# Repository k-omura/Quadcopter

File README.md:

# Quadcopter with PIC18F1230 and ESP8266.
Make a quadcopter from 0.  

PIC18F1230 as the BLDC driver and ESP 8266 as the central control unit.  
Do not use commercially available BLDC ESC.  

----------------------------

# BLDC driver
https://github.com/k-omura/SensorlessBLDC

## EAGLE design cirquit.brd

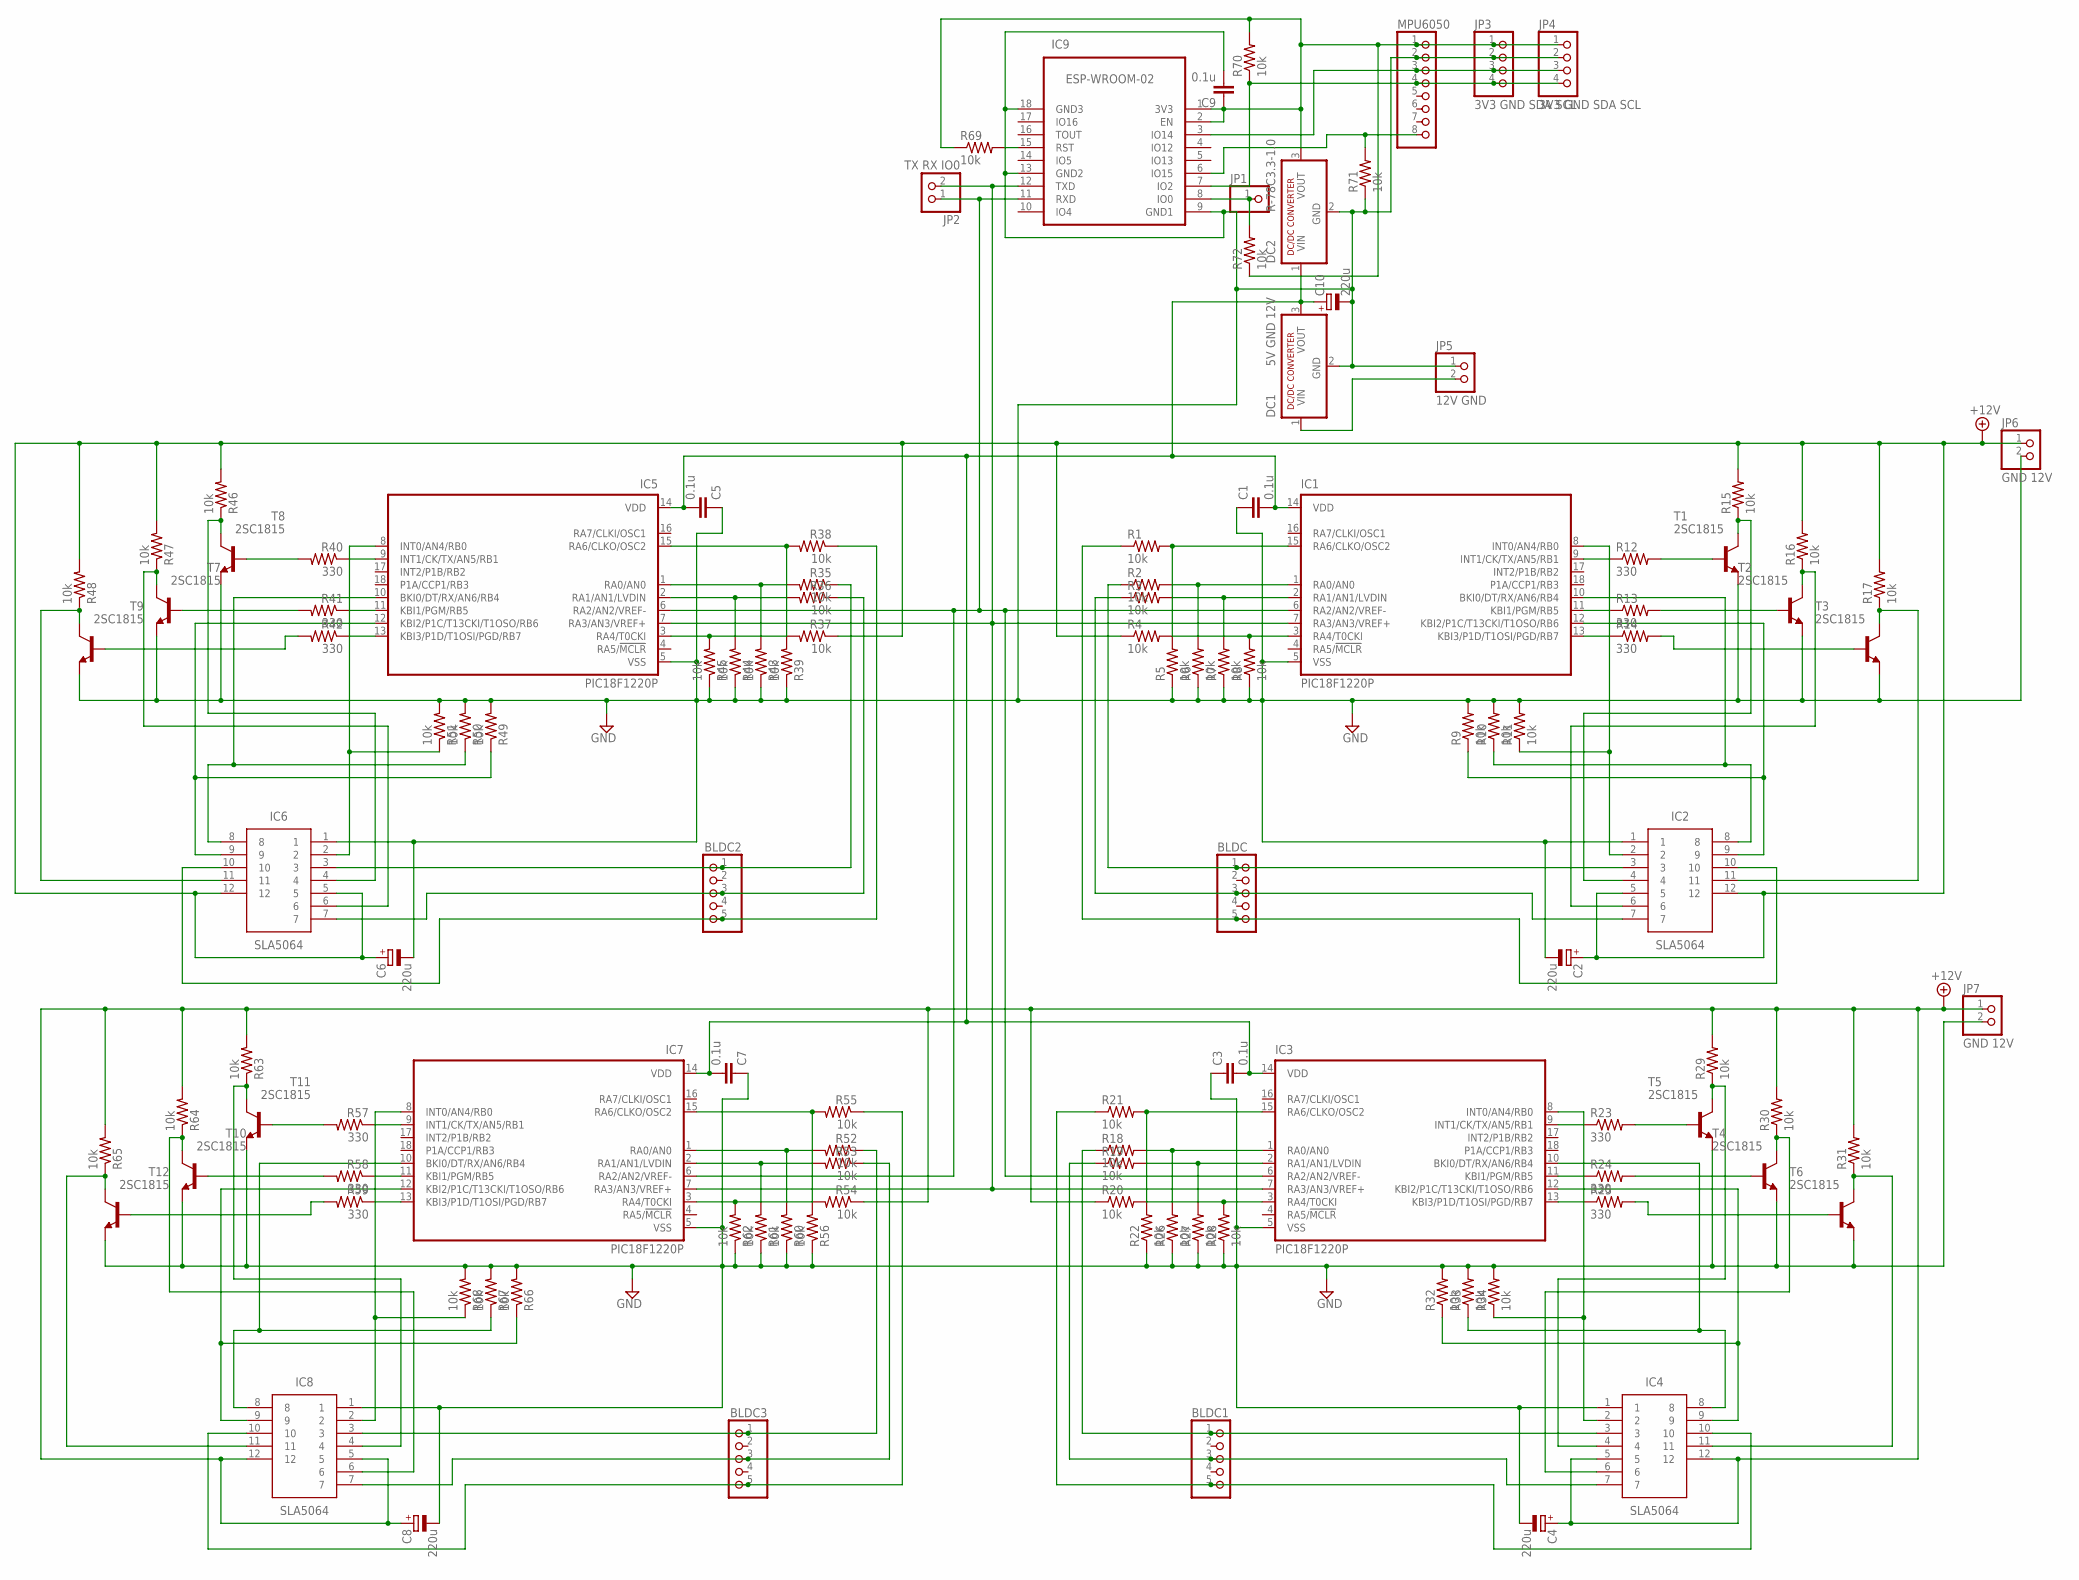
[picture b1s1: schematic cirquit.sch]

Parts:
BLDC, BLDC1, BLDC2, BLDC3: PINHD-1X5; 1X05
C1, C3, C5, C7, C9: 0.1u; C2.5-2
C2, C4, C6, C8, C10: 220u; E2,5-6E
DC1: 5V GND 12V; SIP3
DC2: R-78C3.3-1.0; SIP3
IC1, IC3, IC5, IC7: PIC18F1220P; DIL18
IC2, IC4, IC6, IC8: SLA5064; TO254P500X3150X1890-12P
IC9: ESP-WROOM-02; FRONT-FACE
JP1: PINHD-1X1; 1X01
JP2: TX RX IO0; 1X02
JP3, JP4: 3V3 GND SDA SCL; 1X04
JP5: 12V GND; 1X02
JP6, JP7: GND 12V; 1X02
MPU6050: PINHD-1X8; 1X08
R1, R2, R3, R4, R5, R6, R7, R8, R9, R10, R11, R15, R16, R17, R18, R19, R20, R21, R22, R26, R27, R28, R29, R30, R31, R32, R33, R34, R35, R36, R37, R38, R39, R43, R44, R45, R46, R47, R48, R49, R50, R51, R52, R53, R54, R55, R56, R60, R61, R62, R63, R64, R65, R66, R67, R68, R69, R70, R71, R72: 10k; 0204/7
R12, R13, R14, R23, R24, R25, R40, R41, R42, R57, R58, R59: 330; 0204/7
T1, T2, T3, T4, T5, T6, T7, T8, T9, T10, T11, T12: 2SC1815; TO92-ECB

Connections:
+12V: C2.+, C4.+, C6.+, C8.+, IC2.5, IC2.12, IC4.5, IC4.12, IC6.5, IC6.12, IC8.5, IC8.12, JP6.1, JP7.1, R4.1, R15.2, R16.2, R17.2, R20.1, R29.2, R30.2, R31.2, R37.1, R46.2, R47.2, R48.2, R54.1, R63.2, R64.2, R65.2
GND: C1.1, C2.-, C3.1, C4.-, C5.1, C6.-, C7.1, C8.-, C9.2, C10.-, DC1.2 (GND), DC2.2 (GND), IC1.5 (VSS), IC2.1, IC3.5 (VSS), IC4.1, IC5.5 (VSS), IC6.1, IC7.5 (VSS), IC8.1, IC9.9 (GND1), IC9.13 (GND2), IC9.18 (GND3), JP3.2, JP4.2, JP5.1, JP6.2, JP7.2, MPU6050.2, R5.1, R6.1, R7.1, R8.1, R9.2, R10.2, R11.2, R22.1, R26.1, R27.1, R28.1, R32.2, R33.2, R34.2, R39.1, R43.1, R44.1, R45.1, R49.2, R50.2, R51.2, R56.1, R60.1, R61.1, R62.1, R66.2, R67.2, R68.2, R71.1, T1.E, T2.E, T3.E, T4.E, T5.E, T6.E, T7.E, T8.E, T9.E, T10.E, T11.E, T12.E
unnamed: IC1.15 (RA6/CLKO/OSC2), R1.2, R5.2
unnamed: IC1.1 (RA0/AN0), R2.2, R6.2
unnamed: IC1.2 (RA1/AN1/LVDIN), R3.2, R7.2
unnamed: IC1.3 (RA4/T0CKI), R4.2, R8.2
unnamed: IC3.15 (RA6/CLKO/OSC2), R21.2, R22.2
unnamed: BLDC.1, IC2.3, R2.1
unnamed: BLDC.3, IC2.7, R3.1
unnamed: IC3.1 (RA0/AN0), R18.2, R26.2
unnamed: IC1.9 (INT1/CK/TX/AN5/RB1), R12.1
unnamed: IC1.11 (KBI1/PGM/RB5), R13.1
unnamed: IC1.13 (KBI3/P1D/T1OSI/PGD/RB7), R14.1
unnamed: R12.2, T1.B
unnamed: R13.2, T2.B
unnamed: R14.2, T3.B
unnamed: IC2.4, R15.1, T1.C
unnamed: IC2.6, R16.1, T2.C
unnamed: IC2.11, R17.1, T3.C
unnamed: IC3.2 (RA1/AN1/LVDIN), R19.2, R27.2
unnamed: IC3.3 (RA4/T0CKI), R20.2, R28.2
unnamed: BLDC1.1, IC4.3, R18.1
unnamed: BLDC1.3, IC4.7, R19.1
unnamed: IC1.8 (INT0/AN4/RB0), IC2.2, R11.1
unnamed: IC1.10 (BKI0/DT/RX/AN6/RB4), IC2.8, R10.1
unnamed: IC1.12 (KBI2/P1C/T13CKI/T1OSO/RB6), IC2.9, R9.1
unnamed: IC1.6 (RA2/AN2/VREF-), IC3.6 (RA2/AN2/VREF-), IC5.6 (RA2/AN2/VREF-), IC7.6 (RA2/AN2/VREF-), IC9.11 (RXD), JP2.1
unnamed: C1.2, C3.2, C5.2, C7.2, C10.+, DC1.3 (VOUT), DC2.1 (VIN), IC1.14 (VDD), IC3.14 (VDD), IC5.14 (VDD), IC7.14 (VDD)
unnamed: IC3.9 (INT1/CK/TX/AN5/RB1), R23.1
unnamed: IC3.11 (KBI1/PGM/RB5), R24.1
unnamed: BLDC.5, IC2.10, R1.1
unnamed: IC3.13 (KBI3/P1D/T1OSI/PGD/RB7), R25.1
unnamed: R23.2, T5.B
unnamed: R24.2, T4.B
unnamed: R25.2, T6.B
unnamed: IC4.4, R29.1, T5.C
unnamed: IC4.6, R30.1, T4.C
unnamed: IC4.11, R31.1, T6.C
unnamed: IC3.8 (INT0/AN4/RB0), IC4.2, R34.1
unnamed: IC3.10 (BKI0/DT/RX/AN6/RB4), IC4.8, R33.1
unnamed: IC3.12 (KBI2/P1C/T13CKI/T1OSO/RB6), IC4.9, R32.1
unnamed: IC5.15 (RA6/CLKO/OSC2), R38.2, R39.2
unnamed: C9.1, DC2.3 (VOUT), IC9.1 (3V3), IC9.2 (EN), JP3.1, JP4.1, MPU6050.1, R69.1, R70.2, R72.1
unnamed: BLDC1.5, IC4.10, R21.1
unnamed: IC5.1 (RA0/AN0), R35.2, R43.2
unnamed: IC5.2 (RA1/AN1/LVDIN), R36.2, R44.2
unnamed: IC5.3 (RA4/T0CKI), R37.2, R45.2
unnamed: BLDC2.1, IC6.3, R35.1
unnamed: BLDC2.3, IC6.7, R36.1
unnamed: IC5.9 (INT1/CK/TX/AN5/RB1), R40.1
unnamed: IC5.11 (KBI1/PGM/RB5), R41.1
unnamed: IC5.13 (KBI3/P1D/T1OSI/PGD/RB7), R42.1
unnamed: R40.2, T8.B
unnamed: R41.2, T7.B
unnamed: R42.2, T9.B
unnamed: IC6.4, R46.1, T8.C
unnamed: IC6.6, R47.1, T7.C
unnamed: IC6.11, R48.1, T9.C
unnamed: IC5.8 (INT0/AN4/RB0), IC6.2, R51.1
unnamed: IC5.10 (BKI0/DT/RX/AN6/RB4), IC6.8, R50.1
unnamed: IC5.12 (KBI2/P1C/T13CKI/T1OSO/RB6), IC6.9, R49.1
unnamed: IC1.7 (RA3/AN3/VREF+), IC3.7 (RA3/AN3/VREF+), IC5.7 (RA3/AN3/VREF+), IC7.7 (RA3/AN3/VREF+), IC9.12 (TXD), JP2.2
unnamed: DC1.1 (VIN), JP5.2
unnamed: BLDC2.5, IC6.10, R38.1
unnamed: IC7.15 (RA6/CLKO/OSC2), R55.2, R56.2
unnamed: IC7.1 (RA0/AN0), R52.2, R60.2
unnamed: IC7.2 (RA1/AN1/LVDIN), R53.2, R61.2
unnamed: IC7.3 (RA4/T0CKI), R54.2, R62.2
unnamed: BLDC3.1, IC8.3, R52.1
unnamed: BLDC3.3, IC8.7, R53.1
unnamed: IC7.9 (INT1/CK/TX/AN5/RB1), R57.1
unnamed: IC7.11 (KBI1/PGM/RB5), R58.1
unnamed: IC7.13 (KBI3/P1D/T1OSI/PGD/RB7), R59.1
unnamed: R57.2, T11.B
unnamed: R58.2, T10.B
unnamed: R59.2, T12.B
unnamed: IC8.4, R63.1, T11.C
unnamed: IC8.6, R64.1, T10.C
unnamed: IC8.11, R65.1, T12.C
unnamed: IC7.8 (INT0/AN4/RB0), IC8.2, R68.1
unnamed: IC7.10 (BKI0/DT/RX/AN6/RB4), IC8.8, R67.1
unnamed: IC7.12 (KBI2/P1C/T13CKI/T1OSO/RB6), IC8.9, R66.1
unnamed: IC9.3 (IO14), JP3.3, JP4.3, MPU6050.3
unnamed: BLDC3.5, IC8.10, R55.1
unnamed: IC9.7 (IO2), JP3.4, JP4.4, MPU6050.4, R70.1
unnamed: IC9.6 (IO15), MPU6050.8, R71.2
unnamed: IC9.15 (RST), R69.2
unnamed: IC9.8 (IO0), JP1.1, R72.2

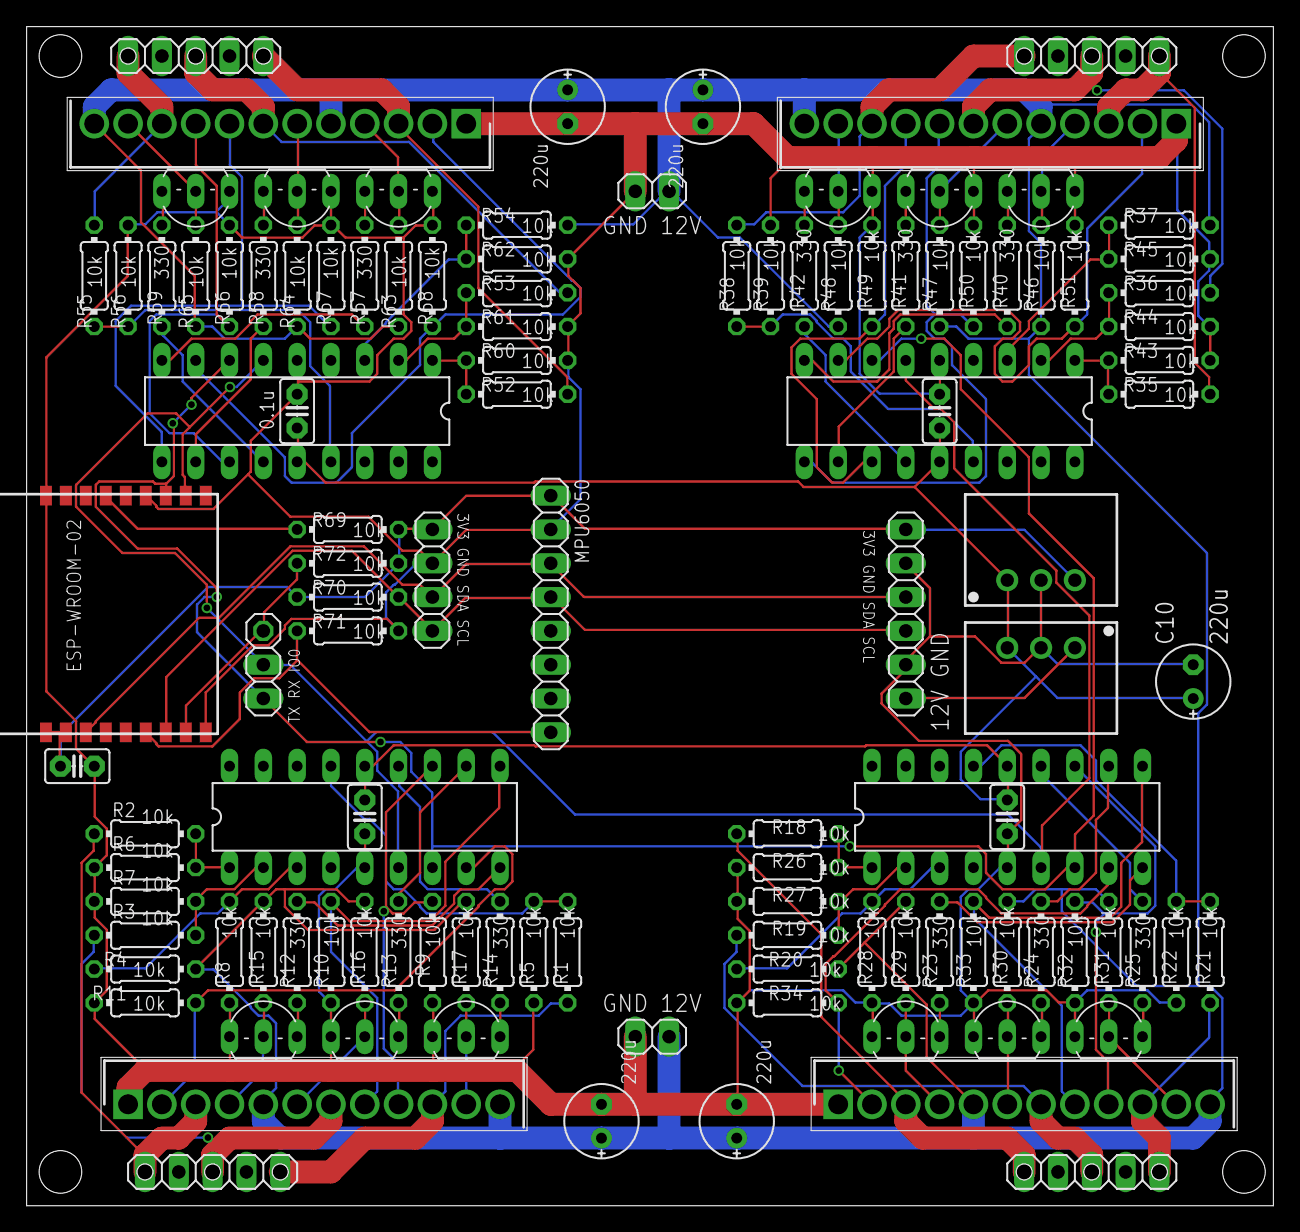
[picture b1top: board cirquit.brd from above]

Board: 2 copper layers, 93.7 x 88.6 mm, 117 parts (0 on the bottom side), 88 nets.

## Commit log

2017-11-26 Main Arduino file
    For testing circuits around the motor
2017-11-26 Rename ESPDroneCentralUnit.ino to testMotor.ino
2017-12-06 controller
    access this on browser
2017-12-06 Rename ESPDroneCentralUnit/index.html to ESPDroneCentralUnit/data/index.html
    ESP flash upload
2017-12-16 BLDC driver for PIC18F1230
    Same as Sensorless BLDC project. However, the position to insert 6 bits for motor speed control was changed.
2018-01-01 Rename cirquit.sch to cirquit/cirquit.sch
2018-01-01 Rename cirquit.brd to cirquit/cirquit.brd
2018-08-28 Create LICENSE
